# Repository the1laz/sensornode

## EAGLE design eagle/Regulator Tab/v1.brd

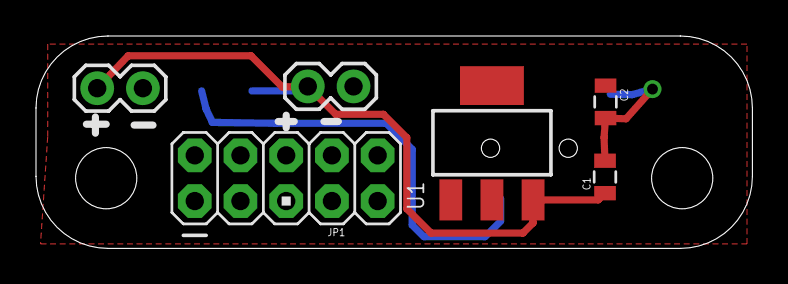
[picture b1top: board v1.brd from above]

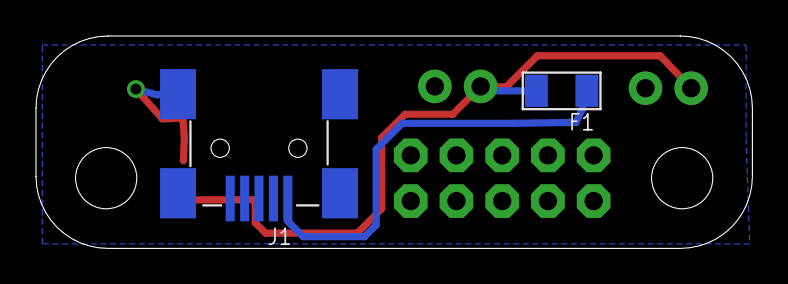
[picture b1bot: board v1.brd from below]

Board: 2 copper layers, 39.8 x 11.8 mm, 8 parts (2 on the bottom side), 4 nets.

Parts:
C1, C2: 0805
F1: 500MA; F1206
J1: MINIUSB5+4P-SMD-0.8-90D
JP1: AVR_ICSP
JP2, JP3: 1X02
U1: PMIC-CJT1117-3.3(SOT223); SOT-223

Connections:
GND: C1.2, C2.2, J1.5, J1.P$1, J1.P$2, J1.P$3, J1.P$4, JP1.1, JP2.2, JP3.2, U1.1
unnamed: F1.1, J1.1
unnamed: C1.1, F1.2, JP2.1, JP3.1, U1.3
VDD: C2.1, JP1.3, U1.2, U1.TER

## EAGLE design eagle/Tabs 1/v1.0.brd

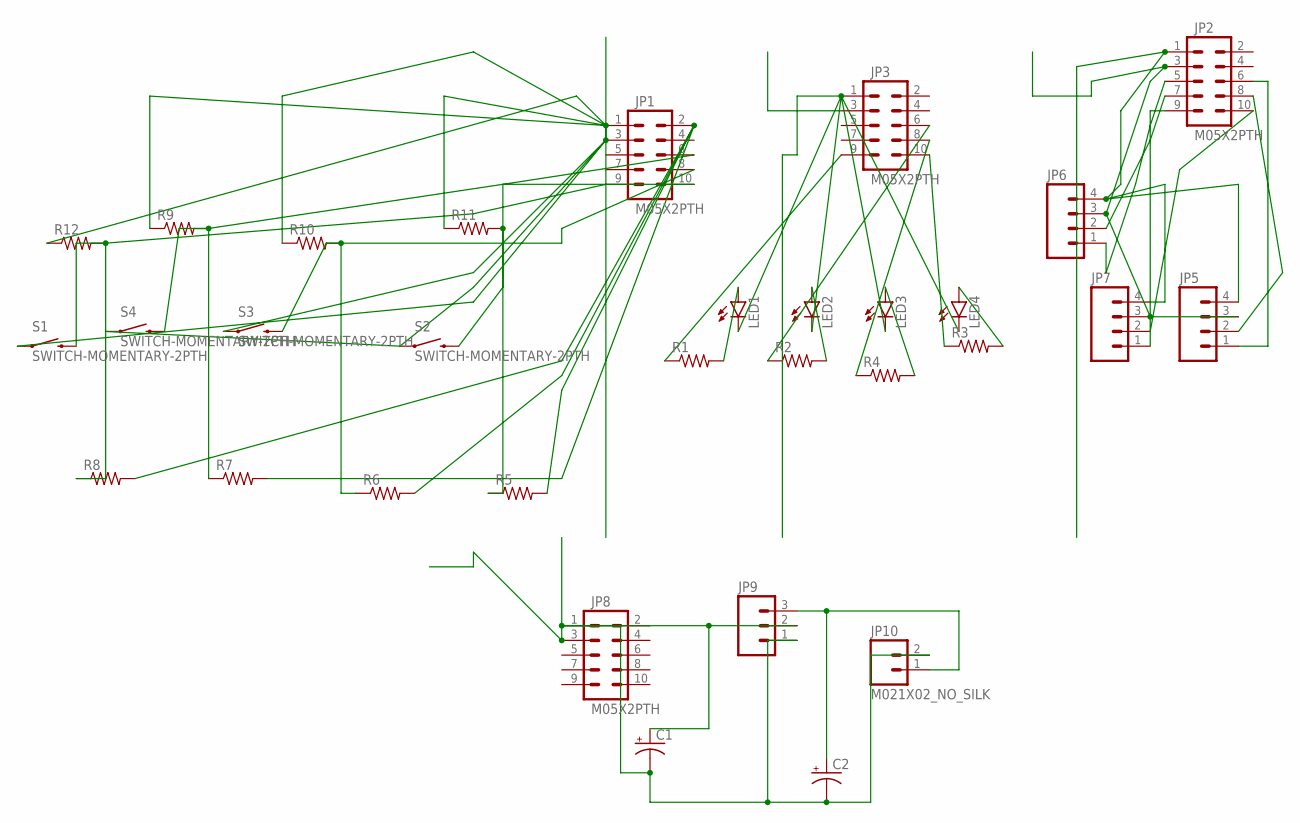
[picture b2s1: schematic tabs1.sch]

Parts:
C1, C2: CAP_POLPTH2; CPOL-RADIAL-10UF-25V
JP1, JP2, JP3, JP8: M05X2PTH; AVR_ICSP
JP5, JP6, JP7: M04POLAR; MOLEX-1X4
JP9: M031X03_NO_SILK; 1X03_NO_SILK
JP10: M021X02_NO_SILK; 1X02_NO_SILK
LED1, LED2, LED3, LED4: LED3MM
R1, R2, R3, R4, R5, R6, R7, R8, R9, R10, R11, R12: RESISTORPTH-1/4W-VERT; AXIAL-0.1
S1, S2, S3, S4: SWITCH-MOMENTARY-2PTH; TACTILE-PTH

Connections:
GND1: C1.2 (-), C2.2 (-), JP8.1, JP9.1, JP10.2
GND2: JP3.1, LED1.K (C), LED2.K (C), LED3.K (C), LED4.K (C)
GND3: JP1.1, R9.P$1 (1), R10.P$1 (1), R11.P$1 (1), R12.P$1 (1)
GND4: JP2.1, JP5.4, JP6.4, JP7.4
unnamed: JP2.5, JP6.1
unnamed: JP2.7, JP6.2
unnamed: JP1.6, R7.P$1 (1), R9.P$2 (2), S4.3 (2)
unnamed: JP1.8, R6.P$1 (1), R10.P$2 (2), S3.3 (2)
unnamed: JP1.9, R8.P$1 (1), R12.P$2 (2), S1.3 (2)
unnamed: JP1.2, R5.P$2 (2), R6.P$2 (2), R7.P$2 (2), R8.P$2 (2)
unnamed: JP2.8, JP5.2
unnamed: LED4.A, R3.P$2 (2)
unnamed: LED3.A, R4.P$2 (2)
unnamed: LED2.A, R2.P$2 (2)
unnamed: LED1.A, R1.P$2 (2)
unnamed: JP3.9, R1.P$1 (1)
unnamed: JP3.6, R2.P$1 (1)
unnamed: JP3.8, R4.P$1 (1)
unnamed: JP3.10, R3.P$1 (1)
unnamed: JP1.10, R5.P$1 (1), R11.P$2 (2), S2.3 (2)
unnamed: JP2.6, JP5.1
unnamed: JP2.10, JP7.2
unnamed: JP2.9, JP7.1
unnamed: C2.1 (+), JP9.3, JP10.1
VCC1: C1.1 (+), JP8.3, JP9.2
VCC2: JP3.3
VCC3: JP1.3, S1.1, S2.1, S3.1, S4.1
VCC4: JP2.3, JP5.3, JP6.3, JP7.3

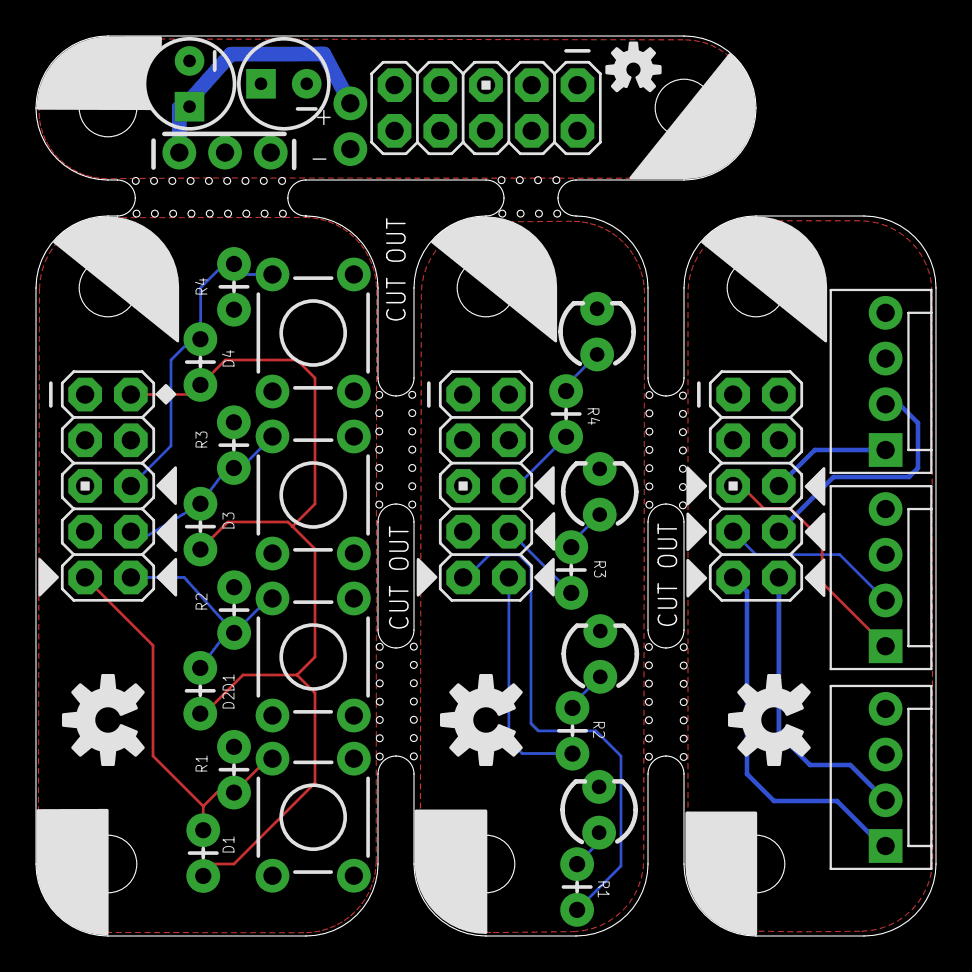
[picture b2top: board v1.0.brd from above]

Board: 2 copper layers, 50.0 x 50.0 mm, 43 parts (0 on the bottom side), 27 nets.

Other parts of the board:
U$1, U$2, U$3, U$4: DP4010_V1_NOLINES
U$5, U$6, U$7: PI
U$8, U$9, U$10: OSHW-LOGO-M
U$11: OSHW-LOGO-S
U$12: PI_XS

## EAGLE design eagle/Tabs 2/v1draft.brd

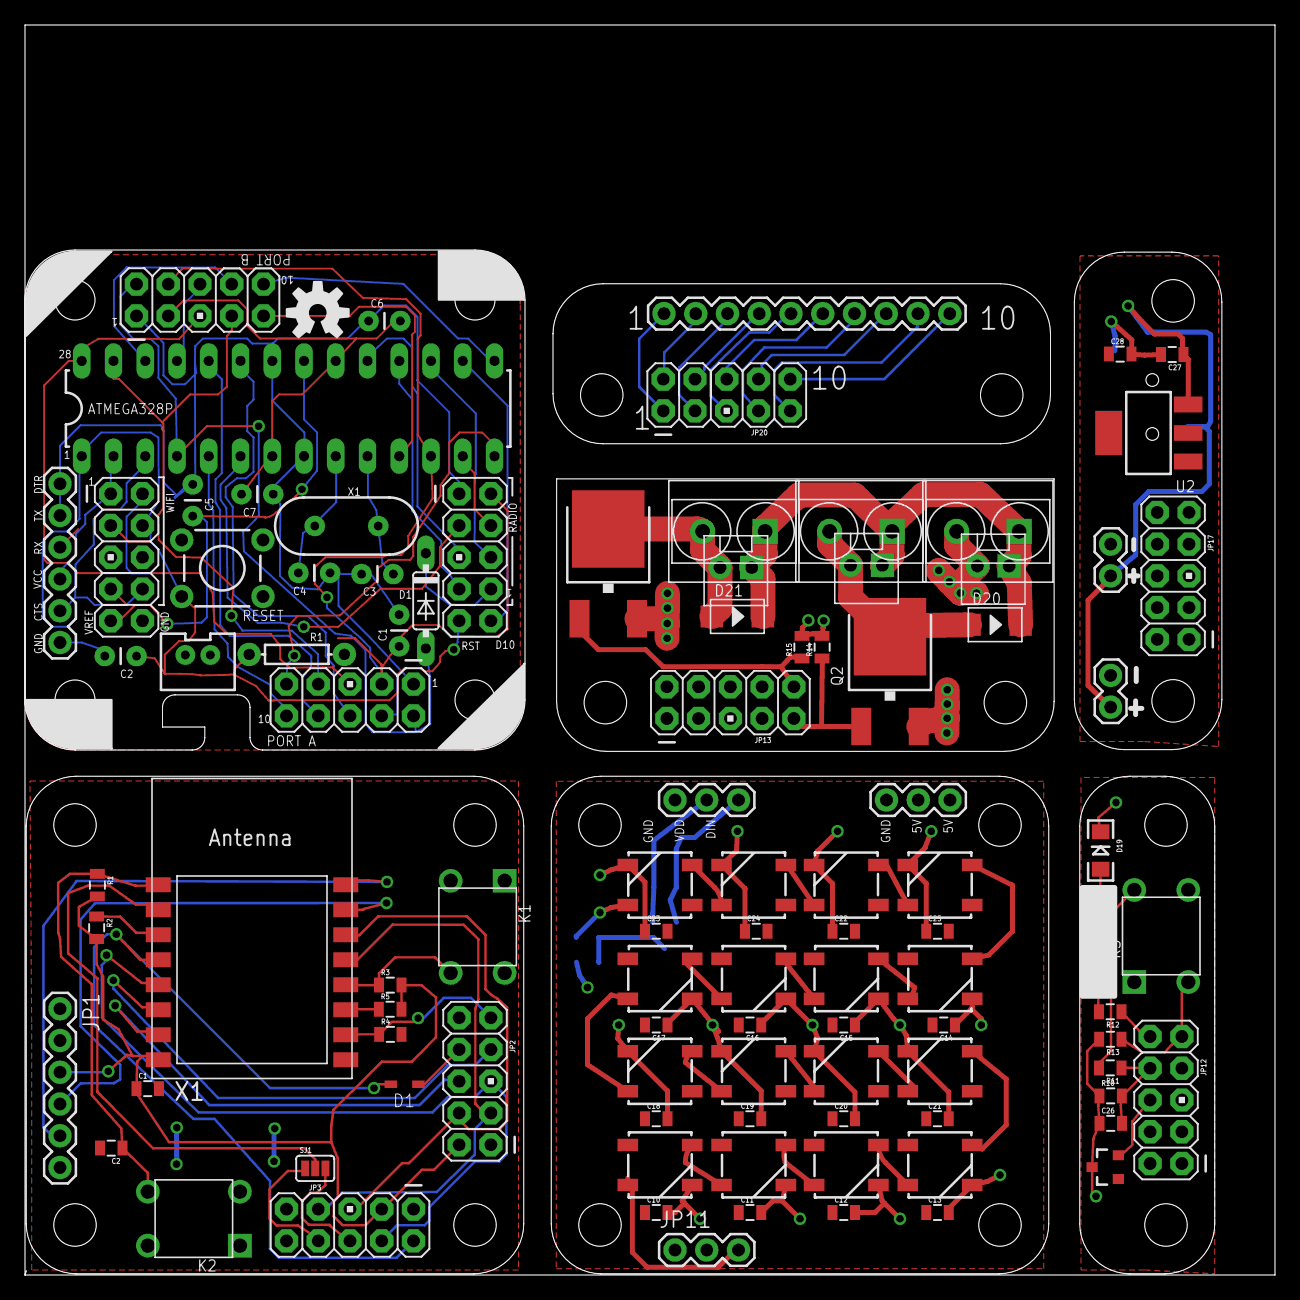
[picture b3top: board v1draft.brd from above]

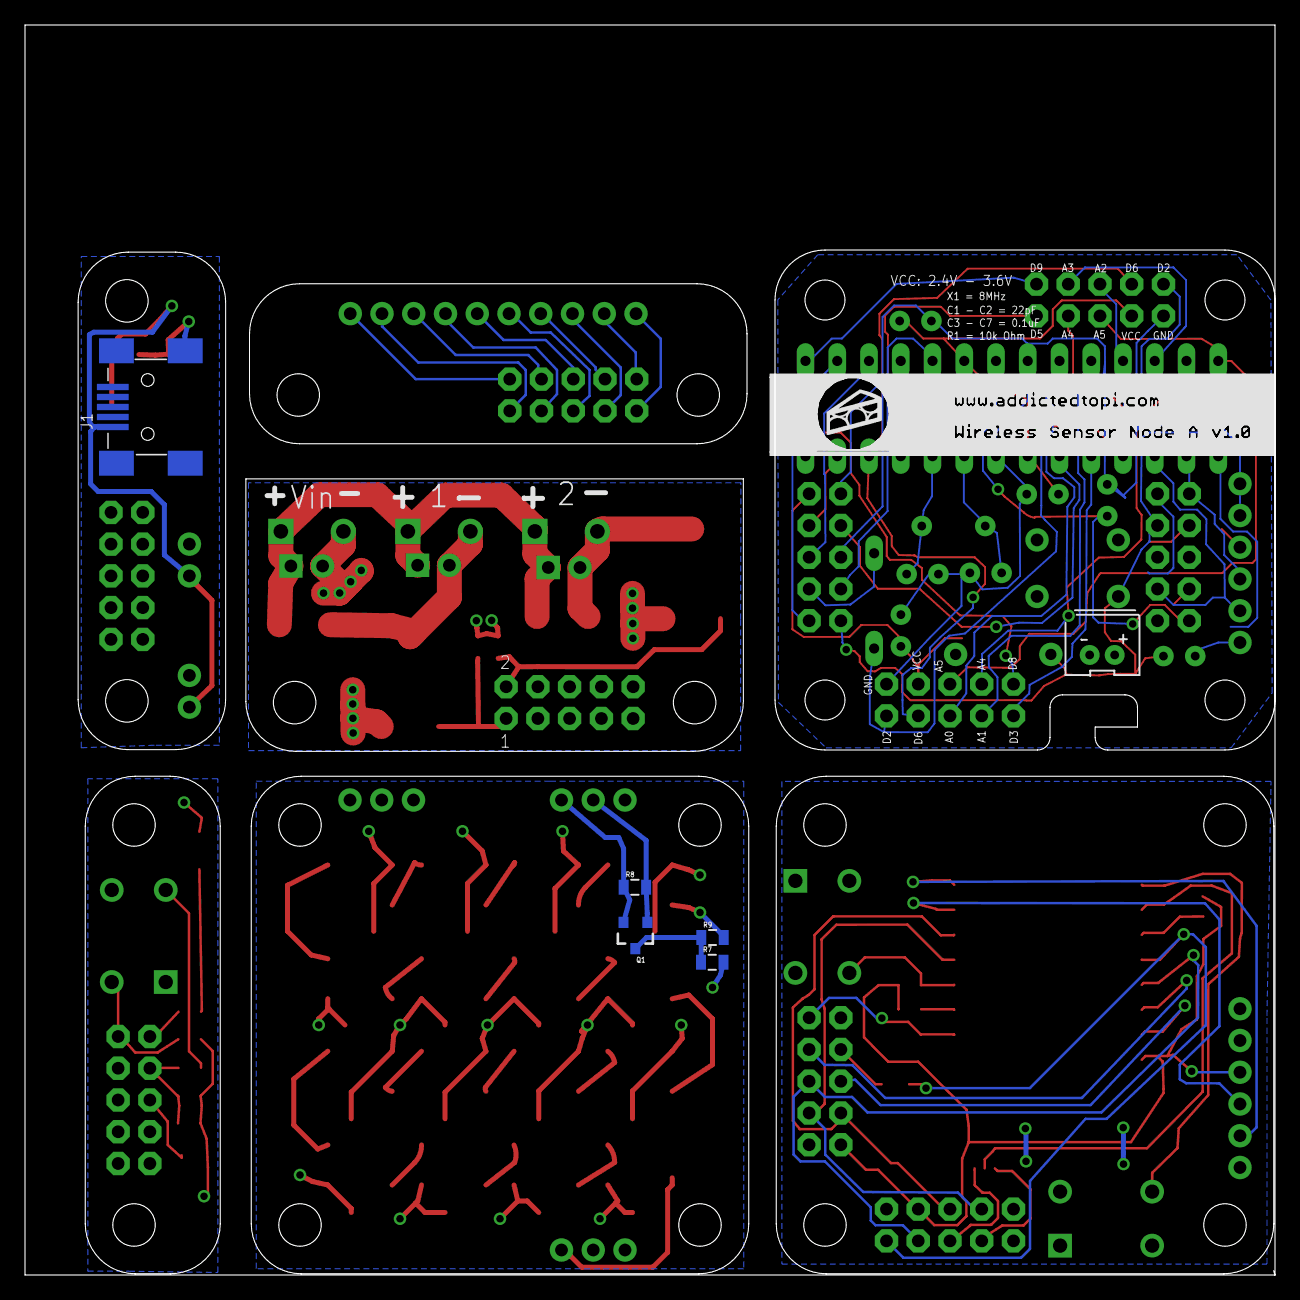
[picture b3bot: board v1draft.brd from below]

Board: 2 copper layers, 100.0 x 100.0 mm, 106 parts (5 on the bottom side), 95 nets.

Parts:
C1, C2, C10, C11, C12, C13, C14, C15, C16, C17, C18, C19, C20, C21, C22, C23, C24, C25, C26, C27, C28: 0805
C3, C4, C5, C6, C7, C8, C9: CAP-PTH-SMALL
D1: SOD323
D2: 1N4148DO35-7; DO35-7
D3, D4, D5, D6, D7, D8, D9, D10, D11, D12, D13, D14, D15, D16, D17, D18: WS2812B
D19: LED-1206
D20, D21: DIODE-GEN-PURPOSE-1KV-1A(DO-214AC); DO-214AC
J1: MINIUSB5+4P-SMD-0.8-90D
JP1, JP6: 1X06
JP2, JP3, JP12, JP13, JP17, JP20: AVR_ICSP
JP4, JP5, JP8: M05X2PTH; AVR_ICSP
JP7: M02JST-PTH-VERT; JST-2-PTH-VERT
JP9, JP10, JP11: 1X03
JP14, JP15, JP16: MOLEX-1X2
JP18, JP19: 1X02
JP21: 1X10
K1, K2, K3: TS-1109; SW4-6.0X6.0X5.0MM
Q1: 200mA/50V; SOT23-3
Q2, Q3: 40V 51A; DPAK
R1, R2, R3, R4, R5, R7, R8, R9, R10, R11, R12, R13, R14, R15: 0805
R6: AXIAL-0.3
RESET: SWITCH-MOMENTARY-2PTH; TACTILE-PTH
RF24: M05X2PTH; AVR_ICSP
SJ1: JUMPER-PAD-3-NOYES_SILK; PAD-JUMPER-3-NO_YES_SILK
U1: ATMEGA328P_PDIP; DIL28-3
U2: PMIC-CJT1117-3.3(SOT223); SOT-223
U$1: DP4040_V1_NOLINES
U$2: MCP9700SMD; SOT23-3
U$3, U$4, U$7: 2p-5.08; H2-5.0-10.5X8.0MM
U$5: PI
U$6: OSHW-LOGO-M
X1: ESP-12
Y1: HC49US

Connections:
3.3V: JP10.2, Q1.1, R8.2
ADC: SJ1.2, X1.2
DIN: JP10.3, Q1.2, R8.1
GND: C1.2, C2.2, JP1.1, JP1.2, JP2.1, JP3.1, K1.4, K2.4, R4.2, X1.9
GND1: C3.2, C5.2, C6.2, C7.2, C8.2, C9.2, JP4.1, JP5.1, JP6.1, JP6.2, JP7.2, JP8.2, JP8.10, RESET.1, RF24.1, U1.8, U1.22
GND2: C26.1, D19.C, JP12.1, R10.1, R13.2, U$2.3
GND3: JP13.1, JP16.2, Q2.2, Q3.2, R14.2, R15.2, U$7.2
GND4: C27.2, C28.2, J1.5, J1.P$1, J1.P$2, J1.P$3, J1.P$4, JP17.1, JP18.2, JP19.2, U2.1
GPIO0: K1.3, R3.1, X1.12
GPIO2: R5.1, X1.11
GPIO4: JP2.3, JP3.7, X1.13
GPIO5: JP2.4, JP3.5, X1.14
GPIO14: JP2.5, JP3.4, X1.5
GPIO16: D1.2, JP3.2, X1.4
unnamed: JP1.5, X1.16
unnamed: JP1.4, X1.15
unnamed: D2.A, JP4.2, JP5.2, U1.4
unnamed: JP3.6, SJ1.3
unnamed: JP2.7, X1.6
unnamed: JP2.6, X1.7
unnamed: JP3.8, SJ1.1
unnamed: C6.1, U1.9, Y1.2
unnamed: D1.1, JP2.8
unnamed: C2.1, K2.3, R1.1, X1.1
unnamed: R2.1, X1.3
unnamed: C5.1, U1.10, Y1.1
unnamed: C7.1, JP8.9, U1.21
unnamed: C4.2, JP6.6
unnamed: C4.1, JP8.4, R6.P$2, RESET.3, RF24.9, U1.1
unnamed: RF24.10, U1.16
unnamed: JP4.4, JP5.4, U1.12
unnamed: JP6.5, JP8.8, U1.3
unnamed: JP6.4, JP8.1, U1.2
unnamed: JP5.6, U1.23
unnamed: JP4.5, JP5.5, U1.28
unnamed: JP4.7, JP5.7, U1.27
unnamed: JP5.8, U1.24
unnamed: D2.C, RF24.8
unnamed: JP4.6, U1.25
unnamed: JP4.8, U1.26
unnamed: JP5.10, U1.5
unnamed: RF24.4, U1.13
unnamed: RF24.5, U1.19
unnamed: RF24.7, U1.18
unnamed: JP5.9, U1.14
unnamed: RF24.6, U1.17
unnamed: RF24.3, U1.6
unnamed: JP4.10, U1.15
unnamed: JP4.9, U1.11
unnamed: D5.4, D6.2
unnamed: D4.4, D5.2
unnamed: D3.4, D4.2
unnamed: D11.4, D12.2
unnamed: D10.4, D11.2
unnamed: D10.2, D18.4
unnamed: D6.4, D13.2
unnamed: D7.2, D12.4
unnamed: D3.2, D17.4
unnamed: D9.4, D17.2
unnamed: D8.4, D9.2
unnamed: D7.4, D8.2
unnamed: D15.4, D16.2
unnamed: D14.4, D15.2
unnamed: D13.4, D14.2
unnamed: D16.4, R9.2
unnamed: D18.2, JP11.3
unnamed: Q1.3, R7.1, R9.1
unnamed: JP12.9, K3.2, R13.1
unnamed: D19.A, R12.2
unnamed: JP12.10, R12.1
unnamed: JP12.6, U$2.2
unnamed: C26.2, JP12.8, R10.2, R11.1
unnamed: D20.2, D21.2, JP14.1, JP15.1, JP16.1, U$3.1, U$4.1, U$7.1
unnamed: D21.1, JP15.2, Q3.3, U$4.2
unnamed: D20.1, JP14.2, Q2.3, U$3.2
unnamed: JP13.9, Q2.1, R14.1
unnamed: JP13.10, Q3.1, R15.1
unnamed: C27.1, J1.1, JP18.1, JP19.1, U2.3
unnamed: JP20.1, JP21.1
unnamed: JP20.3, JP21.3
unnamed: JP20.5, JP21.5
unnamed: JP20.7, JP21.7
unnamed: JP20.9, JP21.9
unnamed: JP20.10, JP21.10
unnamed: JP20.8, JP21.8
unnamed: JP20.6, JP21.6
unnamed: JP20.4, JP21.4
unnamed: JP20.2, JP21.2
SPI_CS: JP2.9, R4.1, X1.10
VCC: C1.1, JP1.3, JP2.2, JP3.3, R1.2, R2.2, R3.2, R5.2, X1.8
VCC1: C3.1, C8.1, C9.1, JP4.3, JP5.3, JP6.3, JP7.1, JP8.3, JP8.7, R6.P$1, RF24.2, U1.7, U1.20
VDD: C10.1, C11.1, C12.1, C13.1, C14.2, C15.2, C16.2, C17.2, C18.1, C19.1, C20.1, C21.1, C22.2, C25.2, D3.1, D4.1, D5.1, D6.1, D7.1, D8.1, D9.1, D10.1, D11.1, D12.1, D13.1, D14.1, D15.1, D16.1, D17.1, D18.1, JP9.1, JP9.2, JP11.2, R7.2
VDD1: JP12.3, K3.4, R11.2, U$2.1
VDD2: C28.1, JP17.3, U2.2, U2.TER
VSS: C10.2, C11.2, C12.2, C13.2, C14.1, C15.1, C16.1, C17.1, C18.2, C19.2, C20.2, C21.2, C22.1, C23.1, C24.1, C25.1, D3.3, D4.3, D5.3, D6.3, D7.3, D8.3, D9.3, D10.3, D11.3, D12.3, D13.3, D14.3, D15.3, D16.3, D17.3, D18.3, JP9.3, JP10.1, JP11.1

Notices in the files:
parts and their libraries:
SparkFun-Connectors: Licensing: Creative Commons ShareAlike 4.0 International - https://creativecommons.org/licenses/by-sa/4.0
